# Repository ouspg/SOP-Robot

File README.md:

# Getting started

The robot uses ROS2 (Robot Operating System 2). Read the [ROS2 wiki!](https://docs.ros.org/). Tutorials and how-to guides are worth to check.

Read also [controller](https://control.ros.org/master/index.html) documentation to understand why certain controllers are needed and how they control the motion.
[Here](https://github.com/ros-controls/ros2_control_demos) are ros2 control demo repositories and more documentation about controllers.

## Quick start

SOP-Robot uses [Pixi](https://pixi.prefix.dev/latest/) to install ROS 2 Humble,
Python packages, and build tools into a local `.pixi/` environment.

```console
sudo apt update
sudo apt install -y git curl espeak
curl -fsSL https://pixi.sh/install.sh | bash
git clone --recurse-submodules https://github.com/ouspg/SOP-Robot.git
cd SOP-Robot
pixi run setup-runtime
pixi run build
pixi run robot-fake
```
Setting up Lehmus AI api key:

```console
cp .env.example .env.local
```

```code
LLM_API_KEY=your lehmus ai api key goes here
```

For real Dynamixel hardware, install the U2D2 udev rule once:

```console
pixi run setup-udev
```

The launch tasks source `install/local_setup.bash` for you. If you enter
`pixi shell` for manual ROS commands, source the overlay first:

```console
source install/local_setup.bash
```

Launch the complete demo from one terminal with `pixi run robot-demo-fake`
for simulation or `pixi run robot-demo-real` for real hardware. Press Ctrl+C
in that terminal to stop the stack. See [Robot bring-up](./docs/BRINGUP.md)
for individual components and logging options.

## The Robot

The robot uses dynamixel servos. Servos are controlled via the `robot_hardware` ROS node, which implements the hardware interface for [ros2_control](https://github.com/ros-controls/ros2_control). `robot` package contains the servo controller configurations for the robot. See [robot.yaml](src/robot/controllers/robot.yaml), for example. The head supports `joint_trajectory_controller`. When using this controller, joints can be controlled by sending action messages to the trajectory controller. See [bring up](./docs/BRINGUP.md) for an example of action message.

Joint -> Servo mappings are defined in two files. Configuration file connects servo ID with certain joint. [dynamixel_arm.yaml](config/dynamixel_arm.yaml) is for servos of robot arm and [dynamixel_head.yaml](config/dynamixel_head.yaml) for servos of head.

## Project structure

* `client`  - contains client to send actions for robot hand
* `config`  - dynamixel servo configuration
* `src`  - all packages
  * `src/face_tracker`  - tracks the faces using camera feed and calculates locations and distances of faces and detects mouth movement.
  * `src/inmoov_description`  - robot files, which define the robot geometry and configuration for simulation (URDF, SRDF & rviz configuration)
  * `src/robot`  - robot launch files & servo controller configurations
  * `src/robot_hardware`  - hardware interface for ros2_controller, communicates with U2D2 via dynamixel workbench
  * `src/tts_package`  - Text-to-speech package for finnish speech synthesis
  * `src/sst_package` - Speech-to-text package 
  for finnish speech recognition
  * `src/llm_package` - OpenAI client package used for using llm model with Lehmus AI API
  * `src/unified_arms`- unified node for controlling arms thought serial and hands with topics
  * `src/full_demo` - Main control node for the robot  

While the robot is idle, `full_demo_node` selects an arm action every 120 seconds by
default: a randomized arm-and-hand action 70% of the time, or one of `wave`, `rock`,
`rotate`, and `swingarms` 30% of the time. The `random` action is implemented by
`unified_arms_node` and runs for 40-60 seconds using the original randomized joint ranges.
It does not command the head. The interval can be changed with the
`random_gesture_interval` parameter on `full_demo_node`.

## Servo Table

**Note: Servos can be configured using [Dynamixel Wizard 2.0](https://emanual.robotis.com/docs/en/software/dynamixel/dynamixel_wizard2/)**

Baud rate: 57600, Voltage: 7.5

**Note: You can use Dynamixel Wizard 2.0 to check that servos have enough voltage to operate normally.**

| Servo ID | Model | Joint name                  | Description           |
| -------- | ----- | --------------------------- | --------------------- |
| 1        | XL430 | head_tilt_right_joint       | Head tilt right-side  |
| 2        | XL430 | head_tilt_vertical_joint    | Head tilt up/down     |
| 3        | XL430 | head_tilt_left_joint        | Head tilt left-side   |
| 4        | XL430 | head_pan_joint              | Head turn left/right  |
| 9        | XL320 | eyes_shift_horizontal_joint | Eyes shift left/right |
| 11       | XL320 | eyes_shift_vertical_joint   | Eyes shift up/down    |
| 12       | XL320 | head_jaw_joint              | Open/close jaw        |
| 31       | XL320 | r_thumb_joint               | Open/close thumb      |
| 34       | XL320 | r_index1_joint              | Open/close index      |
| 37       | XL320 | r_middle1_joint             | Open/close middle     |
| 40       | XL320 | r_ring_joint                | Open/close ring       |
| 44       | XL320 | r_pinky_joint               | Open/close pinky      |
| 47       | XL320 | unnamed joint               | Rotate wrist          |

## Cautions
**Note: head tilt range of motion is poor**

**Note: wrist joint seems to overload very easily**

- Reason for this detected during inspection of the mechanical assembly. The hand is installed wrong way to the wrist.

**Note: servo angle limits are not configured**

**Note: Be careful not to move joints too much, limits are not set yet**

## Next steps

1. See [Development](./docs/DEVELOPMENT.md)
2. See [Robot bring-up](./docs/BRINGUP.md)

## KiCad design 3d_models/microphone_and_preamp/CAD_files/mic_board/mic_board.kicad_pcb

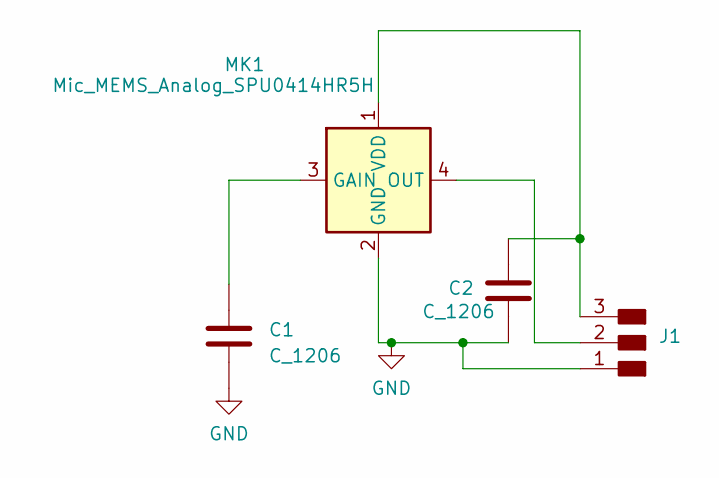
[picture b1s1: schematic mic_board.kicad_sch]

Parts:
C1, C2: C_1206
J1: Conn_PinHeader_1x03_P2.54mm_Horizontal_SMD; PinHeader_1x03_P2.54mm_Vertical_THT_D1mm
MK1: Mic_MEMS_Analog_SPU0414HR5H; Mic_MEMS_Analog_Knowles_SPU0414HR5H

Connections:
GND: C1.2, C2.2, J1.1, MK1.2 (GND)
unnamed: J1.2, MK1.4 (OUT)
unnamed: C2.1, J1.3, MK1.1 (VDD)
unnamed: C1.1, MK1.3 (GAIN)

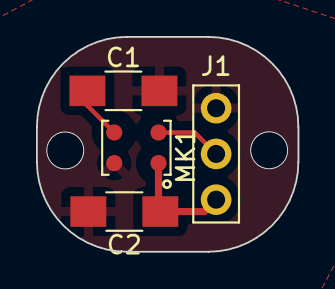
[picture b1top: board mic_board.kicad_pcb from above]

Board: 2 copper layers, 14.5 x 11.9 mm, 4 parts (0 on the bottom side), 4 nets.

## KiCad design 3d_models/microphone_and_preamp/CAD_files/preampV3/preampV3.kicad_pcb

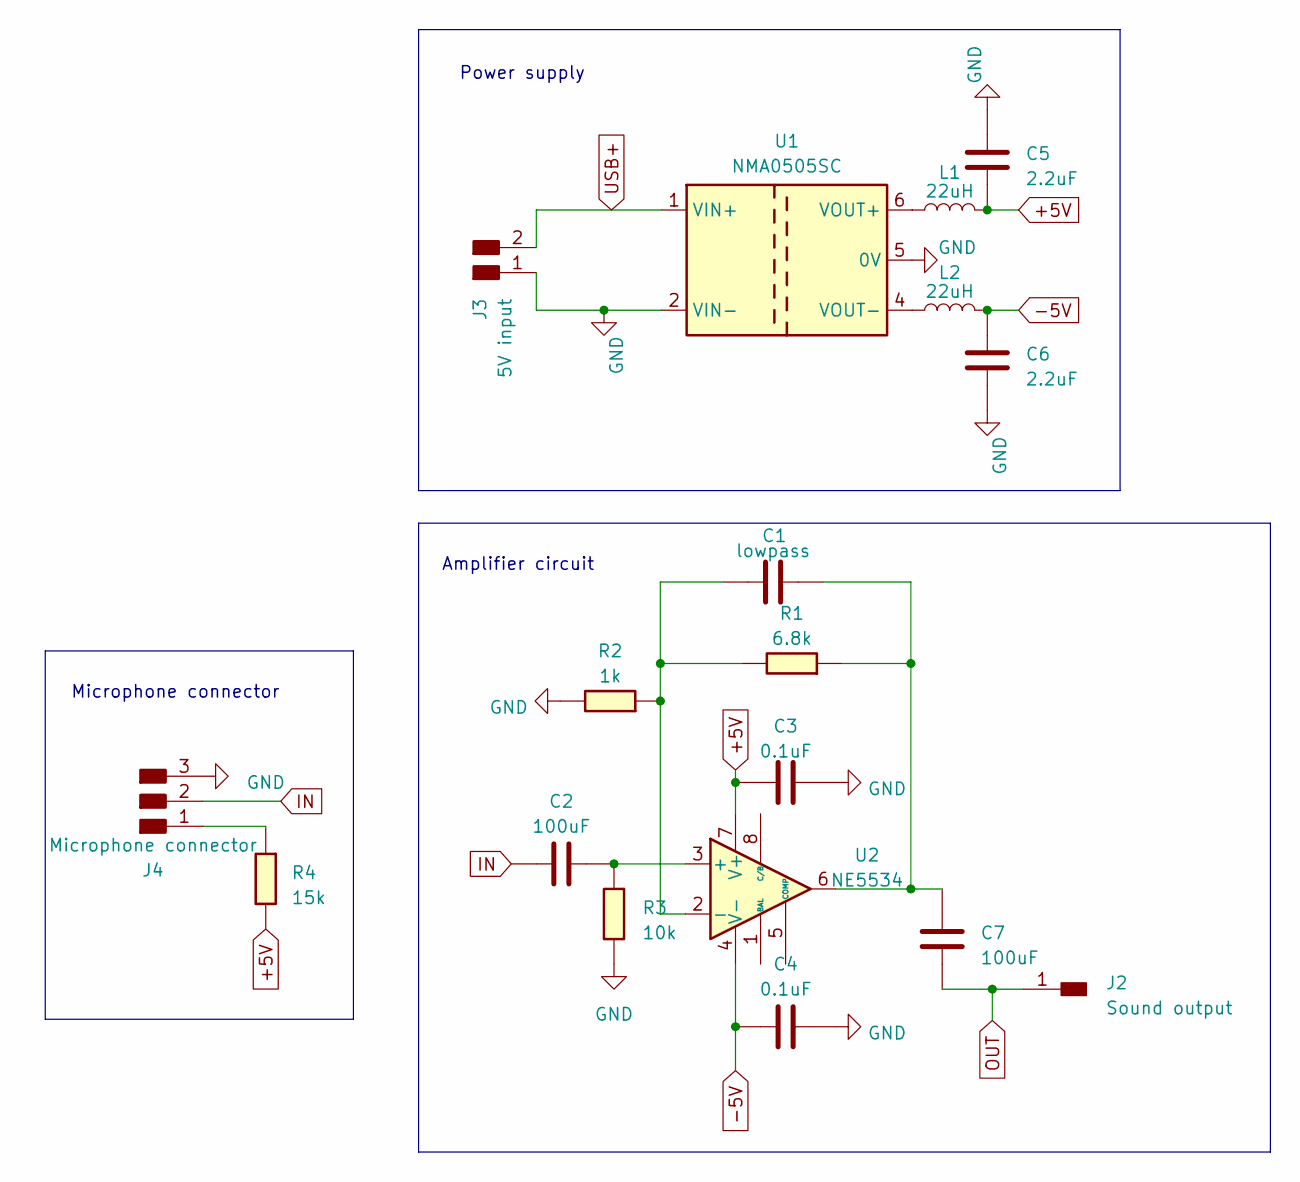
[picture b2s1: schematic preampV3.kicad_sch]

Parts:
C1: lowpass; C_1206
C2, C7: 100uF; C_1206
C3, C4: 0.1uF; C_1206
C5, C6: 2.2uF; C_1206
J2: Sound output; PinHeader_1x01_P2.54mm_Horizontal_SMD
J3: 5V input; PinHeader_1x02_P2.54mm_Horizontal_SMD
J4: Microphone connector; PinHeader_1x03_P2.54mm_Horizontal_SMD
L1, L2: 22uH; L_Wuerth_HCI-7030
R1: 6.8k; R_1206
R2: 1k; R_1206
R3: 10k; R_1206
R4: 15k; R_1206
U1: NMA0505SC; Converter_DCDC_Murata_NMAxxxxSC_THT
U2: NE5534; DIP794W45P254L959H508Q8

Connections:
+5V: C3.1, C5.1, L1.2, R4.1, U2.7 (V+)
-5V: C4.1, C6.1, L2.2, U2.4 (V-)
GND: C3.2, C4.2, C5.2, C6.2, J3.1, J4.3, R2.1, R3.1, U1.2 (VIN-), U1.5 (0V)
IN: C2.1, J4.2
unnamed: C1.2, C7.2, R1.2, U2.6
unnamed: J4.1, R4.2
unnamed: L1.1, U1.6 (VOUT+)
unnamed: L2.1, U1.4 (VOUT-)
unnamed: C2.2, R3.2, U2.3 (+)
unnamed: C1.1, R1.1, R2.2, U2.2 (-)
OUT: C7.1, J2.1; also elsewhere on the board
USB+: J3.2, U1.1 (VIN+)

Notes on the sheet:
Microphone connector
Power supply
Amplifier circuit

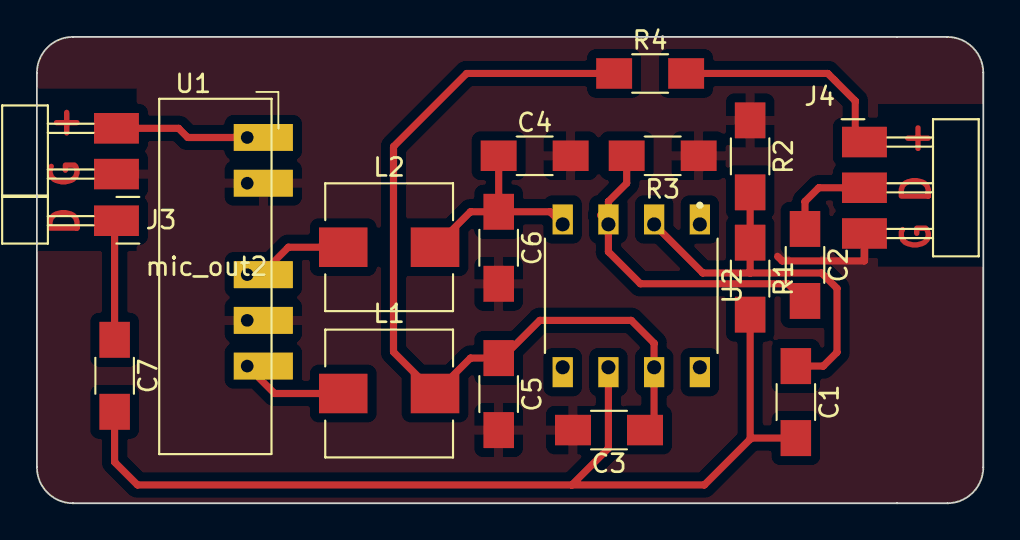
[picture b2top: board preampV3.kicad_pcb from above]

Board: 2 copper layers, 52.6 x 25.9 mm, 18 parts (0 on the bottom side), 12 nets.

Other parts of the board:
mic_out2: Sound output; PinHeader_1x01_P2.54mm_Horizontal_SMD

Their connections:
OUT: mic_out2.1; also elsewhere on the board

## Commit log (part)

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2023-09-18 Uncommented hand joints
2023-09-18 Continued improving face tracking
2023-09-18 Edited comments. TODO: match jaw movement timing to produced speech
2023-09-18 Minor changes to values and limits due to head now being connected to the torso
2023-09-18 Added random idling movement
2023-09-18 Jaw Movement: Made jaw_movement_node run and calculate values and movements only once per input instead of looping indefenitely
2023-09-18 Change jawPos on undefined chars to default to previous char's values
2023-09-18 Fixes for problems
2023-09-22 Added chatbot, speech recognizer and all the rest
2023-10-04 Implement new pretrained finnish QA model, build packages and create nodes
2023-10-10 Added full_demo node
2023-10-12 Upgrade bootstrap.sh chatbot deps
2023-10-18 Remove old chatbot, add context lines to new chatbot
2023-10-20 Add tester for the unified arms controller
2023-10-24 Added qabot files
2023-11-21 Added gestures
2023-11-22 Refactor ifs to match-case
2023-11-22 Modify further to reduce duplicate code
2023-11-25 Added right wrist
2023-12-01 Fix bug preventing sending of commands
2023-12-01 Remove extra lines
2023-12-05 Readme update
2023-12-07 Added README
2024-03-12 Add face_recognition module
2024-03-15 add self.logger definition
2024-03-19 Added argument to switch face_recognizer off
2024-03-22 Update Face class to save image. Move distance comparition into function.
2024-04-03 Remove unnecessary code
2024-04-03 Add filter to fukter too large faces out in face detection
2024-04-08 change bootstrap script to use ansible on vagrant
    Major changes to the previous bootstrap:
    * ansible > 2.10 is required to run the script
    * installation as non-root user under ~/SOP-Robot
    * moving also ros_control to ~/ros_control_ws
    * creation of a non-interactive bash for ansible
    * username defaults now to ansible_env.USER variable and no longer to
2024-04-08 delete vagrant-scripts folder
    Move ros2_control_ws.repos.yml file into ansible-scripts
2024-04-08 WIP rename foxy to humble
    * move roles for ros to separate folder
2024-04-10 move parameters from class parameters to ros node parameters. Parameters moved: lip_movement_detection, face_recognition and correlation_tracking
2024-04-10 Add logging
2024-04-10 modify logging messages
2024-04-24 WIP update launchsettings
    * rename spawner.py to only spawner
    * prefix with xacro to load_yaml files
2024-04-29 Update links cluster and make changes to other code accordingly
2024-04-29 Remove unnecessary code, fix ros messages
2024-05-03 changed face_analyzer init parameters and extract_faces func in face_recognition
2024-05-20 fake robot launch made to work right and cleaned things up
2024-05-21 remove ros foxy setup
    As we now run on humble its basically dead code and can be removed.
2024-09-04 Updated documentation to match the new method
2024-09-16 Fix face_topic
2024-09-16 Update default camera values + update readme
2024-09-16 Add clustering parameters to face_tracker launch parameters.
2024-09-17 Update ansible scripts for face_tracker
2024-10-03 Fix bugs
2024-10-04 self.get_logger() to self.logger.info
2024-10-04 Rename: self.start_eyes_center_position to self.eyes_center_position
2024-10-04 Add missing self.start_eyes_center_position -> self.eyes_center_position
2024-10-11 remove head gestures node from start_robot_head script
2024-10-11 Uncomment eye position logging
2024-10-11 rename /head_gestures/head_gesture_topic to /face_tracker_movement/head_gesture_topic
2024-10-14 added options for future dev
2024-10-15 Syntax fix
2024-10-17 phone detection movement fixed
2024-10-18 Calculate face frames diagonal length and pass that to ros message
2024-10-23 add script: start_robot_head_simulation - this starts the modules needed for the robot head movement
2024-10-23 Add TODO about moving glance to head gestures
2024-10-27 Updated idle timer behavior.
2024-10-28 remove find_threshold, numpy and scipy import
2024-10-29 Fix eye movement bias, fix incorrectly used random.gauss
2024-10-30 should now detect usb disconnect
2024-10-31 added more comments
2024-11-01 Update face tracking to calculate camera angel of movement and divide that for head and eyes. Move glance to gestures
2024-11-01 face tracker improvements
2024-11-04 Improve hello behaviour: logging, add first hello
2024-11-24 small formatting change
2025-06-05 Bump h11 from 0.14.0 to 0.16.0
    Bumps [h11](https://github.com/python-hyper/h11) from 0.14.0 to 0.16.0.
    - [Commits](https://github.com/python-hyper/h11/compare/v0.14.0...v0.16.0)
    ---
    updated-dependencies:
    - dependency-name: h11
    dependency-version: 0.16.0
2025-06-05 Bump torch from 2.4.1 to 2.7.1
    Bumps [torch](https://github.com/pytorch/pytorch) from 2.4.1 to 2.7.1.
    - [Release notes](https://github.com/pytorch/pytorch/releases)
    - [Changelog](https://github.com/pytorch/pytorch/blob/main/RELEASE.md)
    - [Commits](https://github.com/pytorch/pytorch/compare/v2.4.1...v2.7.1)
    ---
    updated-dependencies:
2025-06-18 Bump urllib3 from 1.26.5 to 2.5.0
    Bumps [urllib3](https://github.com/urllib3/urllib3) from 1.26.5 to 2.5.0.
    - [Release notes](https://github.com/urllib3/urllib3/releases)
    - [Changelog](https://github.com/urllib3/urllib3/blob/main/CHANGES.rst)
    - [Commits](https://github.com/urllib3/urllib3/compare/1.26.5...2.5.0)
    ---
    updated-dependencies:
2025-08-22 Bump future from 0.18.2 to 1.0.0
    Bumps [future](https://github.com/PythonCharmers/python-future) from 0.18.2 to 1.0.0.
    - [Release notes](https://github.com/PythonCharmers/python-future/releases)
    - [Changelog](https://github.com/PythonCharmers/python-future/blob/master/docs/changelog.rst)
    - [Commits](https://github.com/PythonCharmers/python-future/compare/v0.18.2...v1.0.0)
    ---
    updated-dependencies:
2025-10-29 Bump keras from 3.6.0 to 3.12.0
    Bumps [keras](https://github.com/keras-team/keras) from 3.6.0 to 3.12.0.
    - [Release notes](https://github.com/keras-team/keras/releases)
    - [Commits](https://github.com/keras-team/keras/compare/v3.6.0...v3.12.0)
    ---
    updated-dependencies:
    - dependency-name: keras
2025-12-16 Bump filelock from 3.6.0 to 3.20.1
    Bumps [filelock](https://github.com/tox-dev/py-filelock) from 3.6.0 to 3.20.1.
    - [Release notes](https://github.com/tox-dev/py-filelock/releases)
    - [Changelog](https://github.com/tox-dev/filelock/blob/main/docs/changelog.rst)
    - [Commits](https://github.com/tox-dev/py-filelock/compare/3.6.0...3.20.1)
    ---
    updated-dependencies:
2026-01-08 Bump werkzeug from 3.0.4 to 3.1.5
    Bumps [werkzeug](https://github.com/pallets/werkzeug) from 3.0.4 to 3.1.5.
    - [Release notes](https://github.com/pallets/werkzeug/releases)
    - [Changelog](https://github.com/pallets/werkzeug/blob/main/CHANGES.rst)
    - [Commits](https://github.com/pallets/werkzeug/compare/3.0.4...3.1.5)
    ---
    updated-dependencies:
2026-01-15 Bump keras from 3.6.0 to 3.13.1
    Bumps [keras](https://github.com/keras-team/keras) from 3.6.0 to 3.13.1.
    - [Release notes](https://github.com/keras-team/keras/releases)
    - [Commits](https://github.com/keras-team/keras/compare/v3.6.0...v3.13.1)
    ---
    updated-dependencies:
    - dependency-name: keras
2026-02-10 Bump cryptography from 3.4.8 to 46.0.5
    Bumps [cryptography](https://github.com/pyca/cryptography) from 3.4.8 to 46.0.5.
    - [Changelog](https://github.com/pyca/cryptography/blob/main/CHANGELOG.rst)
    - [Commits](https://github.com/pyca/cryptography/compare/3.4.8...46.0.5)
    ---
    updated-dependencies:
    - dependency-name: cryptography
2026-03-25 Bump pyasn1 from 0.4.8 to 0.6.3
    Bumps [pyasn1](https://github.com/pyasn1/pyasn1) from 0.4.8 to 0.6.3.
    - [Release notes](https://github.com/pyasn1/pyasn1/releases)
    - [Changelog](https://github.com/pyasn1/pyasn1/blob/main/CHANGES.rst)
    - [Commits](https://github.com/pyasn1/pyasn1/compare/v0.4.8...v0.6.3)
    ---
    updated-dependencies:
2026-03-25 Bump configobj from 5.0.6 to 5.0.9
    Bumps [configobj](https://github.com/DiffSK/configobj) from 5.0.6 to 5.0.9.
    - [Release notes](https://github.com/DiffSK/configobj/releases)
    - [Changelog](https://github.com/DiffSK/configobj/blob/release/CHANGES.rst)
    - [Commits](https://github.com/DiffSK/configobj/compare/v5.0.6...v5.0.9)
    ---
    updated-dependencies:
2026-03-25 Bump twisted from 22.1.0 to 24.7.0rc1
    Bumps [twisted](https://github.com/twisted/twisted) from 22.1.0 to 24.7.0rc1.
    - [Release notes](https://github.com/twisted/twisted/releases)
    - [Changelog](https://github.com/twisted/twisted/blob/twisted-24.7.0rc1/NEWS.rst)
    - [Commits](https://github.com/twisted/twisted/compare/twisted-22.1.0...twisted-24.7.0rc1)
    ---
    updated-dependencies:
2026-03-25 Bump torch from 2.7.1 to 2.8.0
    Bumps [torch](https://github.com/pytorch/pytorch) from 2.7.1 to 2.8.0.
    - [Release notes](https://github.com/pytorch/pytorch/releases)
    - [Changelog](https://github.com/pytorch/pytorch/blob/main/RELEASE.md)
    - [Commits](https://github.com/pytorch/pytorch/compare/v2.7.1...v2.8.0)
    ---
    updated-dependencies:
2026-03-25 Bump pillow from 9.0.1 to 12.1.1
    Bumps [pillow](https://github.com/python-pillow/Pillow) from 9.0.1 to 12.1.1.
    - [Release notes](https://github.com/python-pillow/Pillow/releases)
    - [Changelog](https://github.com/python-pillow/Pillow/blob/main/CHANGES.rst)
    - [Commits](https://github.com/python-pillow/Pillow/compare/9.0.1...12.1.1)
    ---
    updated-dependencies:
2026-03-25 temporary changes
2026-03-29 Bump cryptography from 46.0.5 to 46.0.6
    Bumps [cryptography](https://github.com/pyca/cryptography) from 46.0.5 to 46.0.6.
    - [Changelog](https://github.com/pyca/cryptography/blob/main/CHANGELOG.rst)
    - [Commits](https://github.com/pyca/cryptography/compare/46.0.5...46.0.6)
    ---
    updated-dependencies:
    - dependency-name: cryptography
2026-03-30 Bump pygments from 2.18.0 to 2.20.0
    Bumps [pygments](https://github.com/pygments/pygments) from 2.18.0 to 2.20.0.
    - [Release notes](https://github.com/pygments/pygments/releases)
    - [Changelog](https://github.com/pygments/pygments/blob/master/CHANGES)
    - [Commits](https://github.com/pygments/pygments/compare/2.18.0...2.20.0)
    ---
    updated-dependencies:
2026-03-31 changed submodule
2026-04-08 Bump cryptography from 46.0.5 to 46.0.7
    Bumps [cryptography](https://github.com/pyca/cryptography) from 46.0.5 to 46.0.7.
    - [Changelog](https://github.com/pyca/cryptography/blob/main/CHANGELOG.rst)
    - [Commits](https://github.com/pyca/cryptography/compare/46.0.5...46.0.7)
    ---
    updated-dependencies:
    - dependency-name: cryptography
2026-04-16 added windows support for virtual testing
2026-04-22 temp
2026-04-25 chore(pixi): define ROS workspace tasks
    Move workspace defaults into Pixi activation, split CPU and GPU environments, and switch the build task to the RoboStack Humble/colcon pattern. Add the helper scripts and project-level test/benchmark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
2026-04-25 refactor(perception): group face tracking packages
    Move face tracking, face movement, and face_tracker_msgs under src/sop_robot_perception. Keep package-root node modules as the canonical implementation surface, update entry points and tests, and dro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
2026-04-25 docs: document migrated workspace layout
    Update README, bring-up, development, testing, and voice-contract documentation for the subsystem source layout, Pixi commands, canonical launch entrypoints, and moved vendor packages. Refresh editor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
2026-04-25 chore(legacy): archive retired chatbot packages
    Move the old chatbot, qabot, and speech_recognizer packages under legacy/ with COLCON_IGNORE markers so they stay available as reference data without participating in the active ROS workspace. This a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
2026-04-25 style(ansible): normalize playbook indentation
    Reformat the bootstrap playbook indentation consistently after the TTS resource path update. The parsed YAML structure remains valid.
2026-05-06 Bump twisted from 24.7.0rc1 to 26.4.0rc2
    Bumps [twisted](https://github.com/twisted/twisted) from 24.7.0rc1 to 26.4.0rc2.
    - [Release notes](https://github.com/twisted/twisted/releases)
    - [Changelog](https://github.com/twisted/twisted/blob/trunk/NEWS.rst)
    - [Commits](https://github.com/twisted/twisted/compare/twisted-24.7.0rc1...twisted-26.4.0rc2)
    ---
    updated-dependencies:
2026-05-19 Bump idna from 3.3 to 3.15
    Bumps [idna](https://github.com/kjd/idna) from 3.3 to 3.15.
    - [Release notes](https://github.com/kjd/idna/releases)
    - [Changelog](https://github.com/kjd/idna/blob/master/HISTORY.md)
    - [Commits](https://github.com/kjd/idna/compare/v3.3...v3.15)
    ---
    updated-dependencies:
